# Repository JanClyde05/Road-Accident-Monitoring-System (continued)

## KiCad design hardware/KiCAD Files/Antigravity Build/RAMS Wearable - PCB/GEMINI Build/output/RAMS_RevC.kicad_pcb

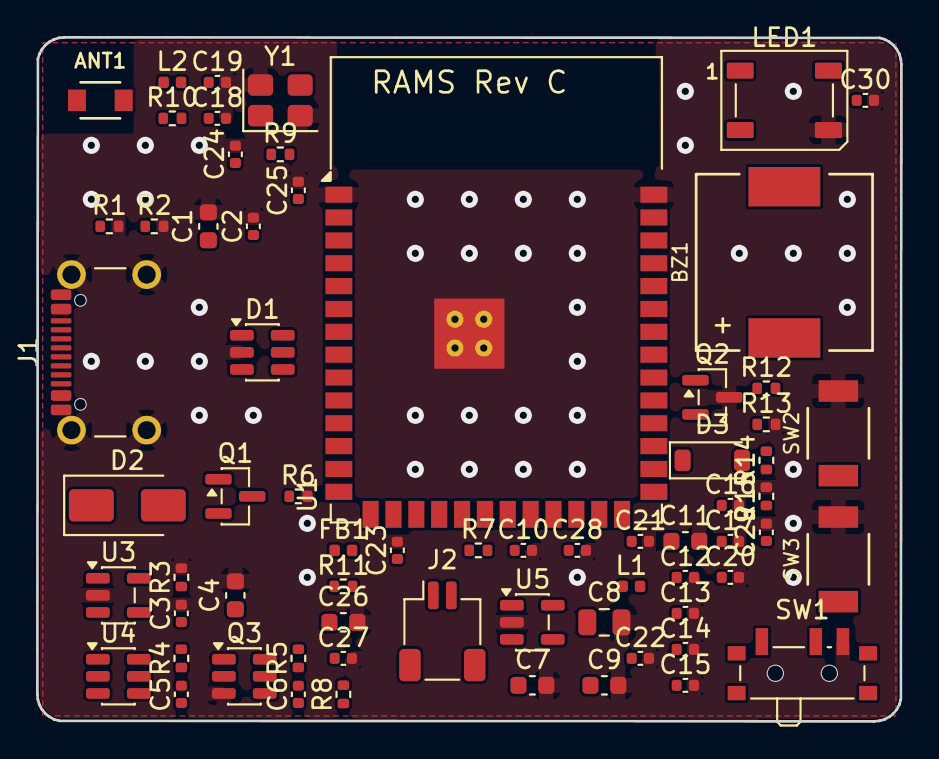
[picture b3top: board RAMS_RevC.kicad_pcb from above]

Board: 2 copper layers, 48.0 x 38.0 mm, 68 parts (1 on the bottom side), 37 nets, no tracks yet.

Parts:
ANT1: 2450AT18B100E; Johanson_2450AT18B100_3216
BZ1: SMD-9650-3327; Buzzer_SMD_9650
C1: 10uF 16V; C_0603_1608Metric
C2, C5, C6, C10, C13, C14, C15, C16, C20, C27, C28, C29, C30: 0.1uF; C_0402_1005Metric
C3, C12, C17, C22, C23: 1uF; C_0402_1005Metric
C4: 4.7uF; C_0603_1608Metric
C7, C9, C11, C26: 10uF; C_0603_1608Metric
C8: 47uF; C_0805_2012Metric
C18, C19: 2.4pF; C_0402_1005Metric
C21: 10nF; C_0402_1005Metric
C24, C25: 12pF; C_0402_1005Metric
D1: USBLC6-2SC6; SOT-23-6
D2: SS14; D_SMA
D3: 1N4148W; D_SOD-123
FB1: FerriteBead; L_0402_1005Metric
J1: TYPE-C-31-M-12; USB_C_16P_USB4105_EPDC
J2: SM02B-SRSS-TB; JST_SH_SM02B-SRSS-TB_1x02-1MP_P1.00mm_Horizontal
L1: 0R (DNP for WROOM-1); L_0402_1005Metric
L2: 2.4nH; L_0402_1005Metric
LED1: WS2812B; LED_WS2812B_PLCC4_5.0x5.0mm_P3.2mm
Q1: AO3401A; SOT-23
Q2: BC817-25; SOT-23
Q3: FS8205A; SOT-23-6
R1, R2: 5.1k; R_0402_1005Metric
R3: 4.3k 1%; R_0402_1005Metric
R4: 330R; R_0402_1005Metric
R5, R12: 1k; R_0402_1005Metric
R6, R7, R13: 100k; R_0402_1005Metric
R8: 10k; R_0402_1005Metric
R9, R11: 33R; R_0402_1005Metric
R10: 0R; R_0402_1005Metric
R14: 330k 1%; R_0402_1005Metric
R15: 180k 1%; R_0402_1005Metric
SW1: MSK12C02; SW_SPDT_PCM12
SW2: RESET; SW_Tactile_SPST_3x4mm
SW3: BOOT; SW_Tactile_SPST_3x4mm
U1: ESP32-S3-WROOM-1-N4; ESP32-S3-WROOM-1_EPDC
U2: Ai-Thinker-Ra-02; Ai-Thinker-Ra-01-LoRa
U3: LTH7R; SOT-23-5
U4: DW01A; SOT-23-6
U5: AP2112K-3.3; SOT-23-5
Y1: 40MHz; Crystal_SMD_3225-4Pin_3.2x2.5mm

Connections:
/+3V3: BZ1.1, C8.1, C9.1, C10.1, C11.1, C12.1, C13.1, C14.1, C15.1, C16.1, C17.1, C20.1, C21.1, C22.1, C28.1, C30.1, D3.1, FB1.1, L1.1, L1.2, LED1.1, R8.2, U1.2, U5.5
/ANT_FEED: ANT1.1, R10.2
/BOOT: SW3.1, U1.27
/BUZZER_BASE: Q2.1, R12.2, R13.1
/BUZZER_DRV: R12.1, U1.39
/BUZZER_NEG: BZ1.2, D3.2, Q2.2
/B_MINUS: C5.2, C6.2, J2.2, Q3.1, R5.2, U4.6
/B_PLUS: C4.1, J2.1, Q1.3, R4.1, R14.1, U3.3
/CC1: J1.A5, R1.1
/CC2: J1.B5, R2.1
/DW_CS: C6.1, R5.1, U4.2
/DW_OC: Q3.4, U4.3
/DW_OD: Q3.6, U4.1
/DW_VCC: C5.1, R4.2, U4.5
/EN: C23.1, R8.1, SW2.1, U1.3
/GND: C1.2, C2.2, C3.2, C4.2, C7.2, C8.2, C9.2, C10.2, C11.2, C12.2, C13.2, C14.2, C15.2, C16.2, C17.2, C18.2, C19.2, C20.2, C21.2, C22.2, C23.2, C24.2, C25.2, C26.2, C27.2, C28.2, C29.2, C30.2, D1.2, J1.A1, J1.A12, J1.B1, J1.B12, J1.SH, LED1.3, Q2.3, Q3.3, R1.2, R2.2, R3.2, R6.2, R13.2, R15.2, SW1.3, SW2.2, SW3.2, U1.1, U1.40, U1.41, U2.1, U2.2, U2.9, U2.16, U3.2, U5.2, Y1.2, Y1.4
/LDO_EN: R7.1, SW1.1, U5.3
/LDO_IN: C7.1, D2.1, Q1.2, R7.2, SW1.2, U5.1
/LED_DIN: LED1.4, U1.25
/LORA_DIO0: U1.12, U2.5
/LORA_MISO: U1.21, U2.13
/LORA_MOSI: U1.19, U2.14
/LORA_NSS: U1.18, U2.15
/LORA_RST: U1.17, U2.4
/LORA_SCK: R11.1, U1.20
/LORA_SCK_DEV: R11.2, U2.12
/LORA_VDD: C26.1, C27.1, FB1.2, U2.3
/PROG: R3.1, U3.5
/Q3_DRAIN: Q3.2, Q3.5
/RF_LNA: C18.1, L2.1
/RF_MID: C19.1, L2.2, R10.1
/USB_DN: D1.1, D1.6, J1.A7, J1.B7, U1.13
/USB_DP: D1.3, D1.4, J1.A6, J1.B6, U1.14
/VBAT_SENSE: C29.1, R14.2, R15.1, U1.38
/VBUS: C1.1, C2.1, C3.1, D1.5, D2.2, J1.A4, J1.A9, J1.B4, J1.B9, Q1.1, R6.1, U3.4
/XTAL_N: C25.1, Y1.3
/XTAL_P: C24.1, R9.1, Y1.1

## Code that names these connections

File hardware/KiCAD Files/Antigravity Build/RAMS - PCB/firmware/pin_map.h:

// RAMS Wearable PCB - GPIO Pin Map
// Source: SPEC section 7, matching prototype firmware
// Date: 2026-10-13, Rev 0.1
#pragma once

#define PIN_BOOT        0   // BOOT / alarm cancel (strapping pin)
#define PIN_BUZZER      1   // Active buzzer via NPN driver
#define PIN_VBAT_SENSE  2   // Battery voltage divider ADC1
#define PIN_LORA_DIO0   8   // Ra-02 DIO0 interrupt
#define PIN_LORA_RST    9   // Ra-02 RESET
#define PIN_LORA_NSS    10  // Ra-02 NSS chip select
#define PIN_LORA_MOSI   11  // SPI MOSI
#define PIN_LORA_SCK    12  // SPI SCK
#define PIN_LORA_MISO   13  // SPI MISO
#define PIN_USB_DN      19  // USB D-
#define PIN_USB_DP      20  // USB D+
#define PIN_LED         48  // SK6805-EC15 DIN

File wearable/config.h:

/*
 * Road Accident Monitoring System — Wearable Configuration
 * ==========================================================
 * All pin assignments, detection thresholds, and compile-time options.
 *
 * Pin map from spec §3.4. Thresholds from spec §6 — these are INITIAL
 * literature-based defaults. Run validate_fsm.py against collected data
 * to derive empirically-tuned values, then update these constants.
 *
 * ┌──────────────────────────────────────────────────────────────────┐
 * │  BEFORE FLASHING:                                                │
 * │  1. Verify NeoPixel GPIO48 against your board's silkscreen      │
 * │  2. Confirm SX1278 logic levels match SuperMini I/O              │
 * └──────────────────────────────────────────────────────────────────┘
 */

#ifndef RAMS_WEARABLE_CONFIG_H
#define RAMS_WEARABLE_CONFIG_H

// ── I2C — MPU-6050 IMU ─────────────────────────────────────────────────────
#define IMU_SDA_PIN       8
#define IMU_SCL_PIN       9
#define IMU_INT_PIN       4     // MPU-6050 interrupt (data-ready)

// ── UART — ATGM336H GPS ────────────────────────────────────────────────────
#define GPS_RX_PIN        17    // ESP32 RX ← GPS TX
#define GPS_TX_PIN        18    // ESP32 TX → GPS RX
#define GPS_BAUD          9600

// ── SPI — Ra-02 LoRa (SX1278) ──────────────────────────────────────────────
#define LORA_NSS_PIN      10
#define LORA_SCK_PIN      12
#define LORA_MISO_PIN     13
#define LORA_MOSI_PIN     11
#define LORA_RST_PIN      14
#define LORA_DIO0_PIN     16

// ── Button — False-alarm / Re-arm / Setup-mode toggle ───────────────────────
// GPIO2 chosen instead of GPIO0 to avoid boot-strapping conflicts.
//#define BUTTON_PIN        2
#define BUTTON_PIN        0   //Temporary Button since it is onboard
#define BUTTON_DEBOUNCE_MS    50     // Debounce window
#define BUTTON_LONG_PRESS_MS  3000   // Hold duration to enter/exit setup mode

// ── Buzzer — Active buzzer, GPIO-driven ─────────────────────────────────────
// Active buzzer: HIGH = on, LOW = off. No PWM tone generation needed.
#define BUZZER_PIN        1

// ── NeoPixel — Onboard status LED ───────────────────────────────────────────
// Most ESP32-S3 SuperMini clones use GPIO48 for the onboard NeoPixel.
// [NOTE] Verify against your specific board's silkscreen — clone boards vary.
#define NEOPIXEL_PIN      48
#define NEOPIXEL_COUNT    1     // Single onboard LED

// ── Strapping Pins — DO NOT USE ─────────────────────────────────────────────
// GPIO0, GPIO3, GPIO45, GPIO46 — reserved by ESP32-S3 boot process.

// ── SoftAP Configuration (Setup Mode) ───────────────────────────────────────
#define SETUP_AP_SSID     "RAMS_Setup"
#define SETUP_AP_CHANNEL  1
#define SETUP_WS_PORT     81    // WebSocket port for setup-mode communication

// ── Detection Thresholds — INITIAL DEFAULTS ─────────────────────────────────
// These values come from fall-detection literature (spec §6).
// Run validate_fsm.py against collected motion data to derive empirically-
// tuned values. Replace these constants with the script's output.
//
// The "good" outcome is that derived thresholds land CLOSE to these defaults —
// it means "confirmed against local data," not "we guessed wrong."

// Fall FSM thresholds
#define FREEFALL_THRESHOLD_G    0.40f   // A_m below this = freefall phase
#define FREEFALL_MIN_DURATION_MS 100    // Sustained freefall before advancing
#define IMPACT_THRESHOLD_G      3.00f  // A_m above this = impact detected
#define IMPACT_WINDOW_MS        500    // Max time after freefall to detect impact
#define STILLNESS_THRESHOLD_G   0.15f  // σ(A_m) below this = post-impact stillness
#define STILLNESS_DURATION_MS   2000   // Stillness must persist this long to confirm

// Skid/slide detection (FSM must be idle)
#define SKID_LATERAL_G          2.00f  // |ay| threshold
#define SKID_ROLL_RATE_DPS      330.0f // |gx| threshold (degrees/second)
#define SKID_MIN_DURATION_MS    200    // Sustained duration to confirm skid

// Direct impact detection (FSM idle, not mid-skid)
#define DIRECT_IMPACT_G         4.50f  // A_m threshold for single-spike impact
#define DIRECT_IMPACT_DEBOUNCE_MS 5000 // Cooldown between direct-impact events

// Environmental detection (rolling buffer analysis, every 1000ms)
#define ENV_BUFFER_SIZE         50     // Rolling buffer sample count
#define ENV_SAMPLE_INTERVAL_MS  1000   // How often to run environmental analysis
#define ENV_GROUND_SHOCK_ACCEL_STD  0.40f  // σ(A_m) threshold for ground shock
#define ENV_GROUND_SHOCK_ORIENT_STD 10.0f  // σ(roll/pitch) max for ground shock
#define ENV_WAVE_MOTION_ACCEL_STD   0.24f  // σ(A_m) threshold for wave motion
#define ENV_WAVE_MOTION_ORIENT_STD  10.0f  // σ(roll/pitch) min for wave motion

// ── System ──────────────────────────────────────────────────────────────────
#define SERIAL_BAUD       115200

// ── Registration ────────────────────────────────────────────────────────────
#define TOKEN_LENGTH      8     // 8-char alphanumeric device token
#define NVS_NAMESPACE     "rams"

#endif // RAMS_WEARABLE_CONFIG_H
